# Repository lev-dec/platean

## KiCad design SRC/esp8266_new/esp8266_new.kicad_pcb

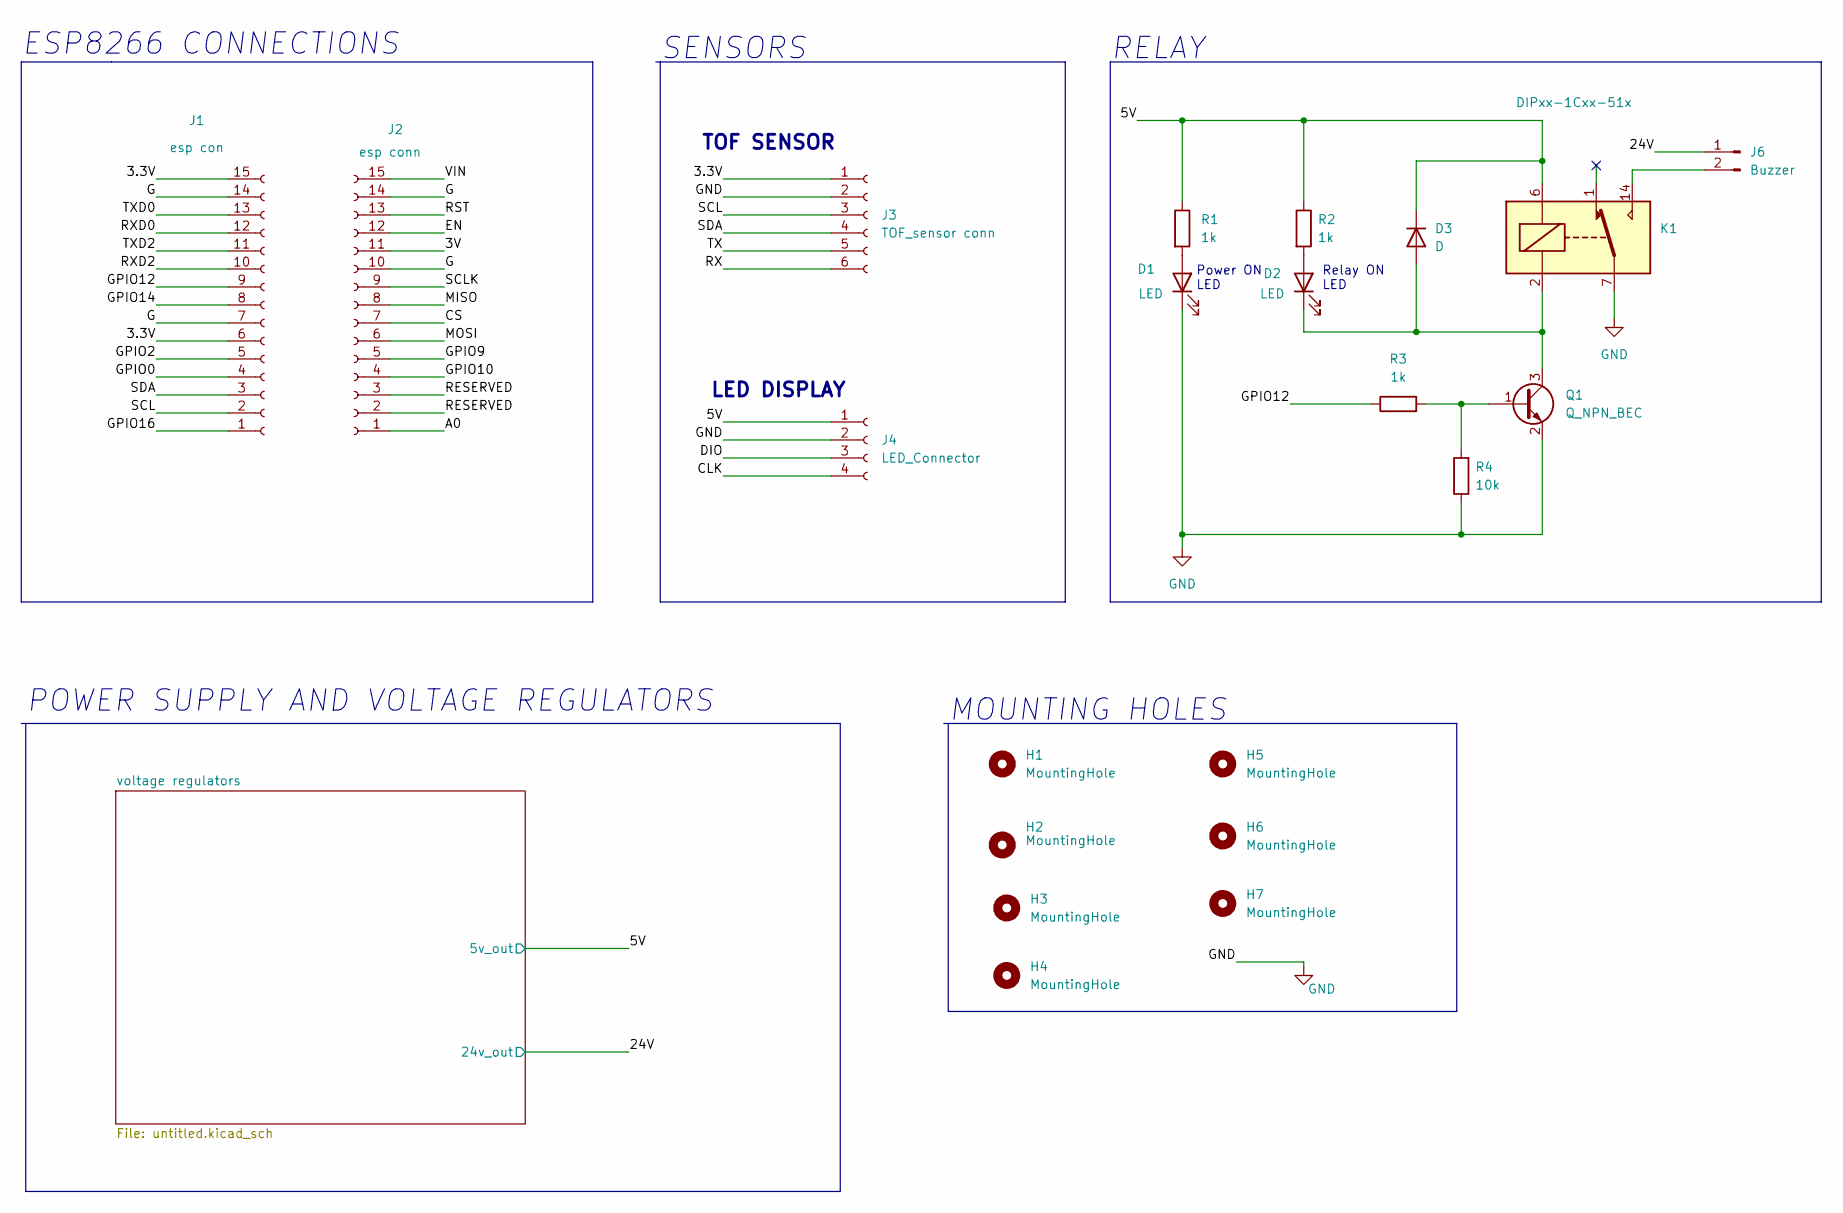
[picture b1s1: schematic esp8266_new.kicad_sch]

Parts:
D1, D2: LED; LED_0603_1608Metric
D3: D; SOT-23
H1, H2, H3, H4, H5, H6, H7: MountingHole; MountingHole_2mm
J1: esp con; PinSocket_1x15_P2.54mm_Vertical
J2: esp conn; PinSocket_1x15_P2.54mm_Vertical
J3: TOF_sensor conn; PinSocket_1x06_P2.54mm_Horizontal
J4: LED_Connector; PinSocket_1x04_P2.54mm_Horizontal
J6: Buzzer; JST_EH_S2B-EH_1x02_P2.50mm_Horizontal
K1: DIPxx-1Cxx-51x; Relay_StandexMeder_DIP_LowProfile
Q1: Q_NPN_BEC; TO-252-3_TabPin2
R1, R2, R3: 1k; R_0603_1608Metric
R4: 10k; R_0603_1608Metric

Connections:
/3.3V: J1.6, J1.15, J3.1
/3V: J2.11
/5V: D3.1 (K), J4.1, K1.6, R1.1, R2.1; also elsewhere on the board
/24V: J6.1; also elsewhere on the board
/A0: J2.1
/CLK: J4.4
/CS: J2.7
/DIO: J4.3
/EN: J2.12
/G: J1.7, J1.14, J2.10, J2.14
/GPIO0: J1.4
/GPIO2: J1.5
/GPIO9: J2.5
/GPIO10: J2.4
/GPIO12: J1.9, R3.1
/GPIO14: J1.8
/GPIO16: J1.1
/MISO: J2.8
/MOSI: J2.6
/RESERVED: J2.2, J2.3
/RST: J2.13
/RX: J3.6
/RXD0: J1.12
/RXD2: J1.10
/SCL: J1.2, J3.3
/SCLK: J2.9
/SDA: J1.3, J3.4
/TX: J3.5
/TXD0: J1.13
/TXD2: J1.11
/VIN: J2.15
GND: D1.1 (K), J3.2, J4.2, K1.7, K1.8, Q1.2 (E), R4.1; also elsewhere on the board
unnamed: D1.2 (A), R1.2
unnamed: D2.1 (K), D3.2 (A), K1.2, Q1.3 (C)
unnamed: D2.2 (A), R2.2
unnamed: J6.2, K1.14
unnamed: Q1.1 (B), R3.2, R4.2

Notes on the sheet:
LED DISPLAY
TOF SENSOR
Relay ON LED
POWER SUPPLY AND VOLTAGE REGULATORS
SENSORS
Power ON LED
MOUNTING HOLES
RELAY
ESP8266 CONNECTIONS

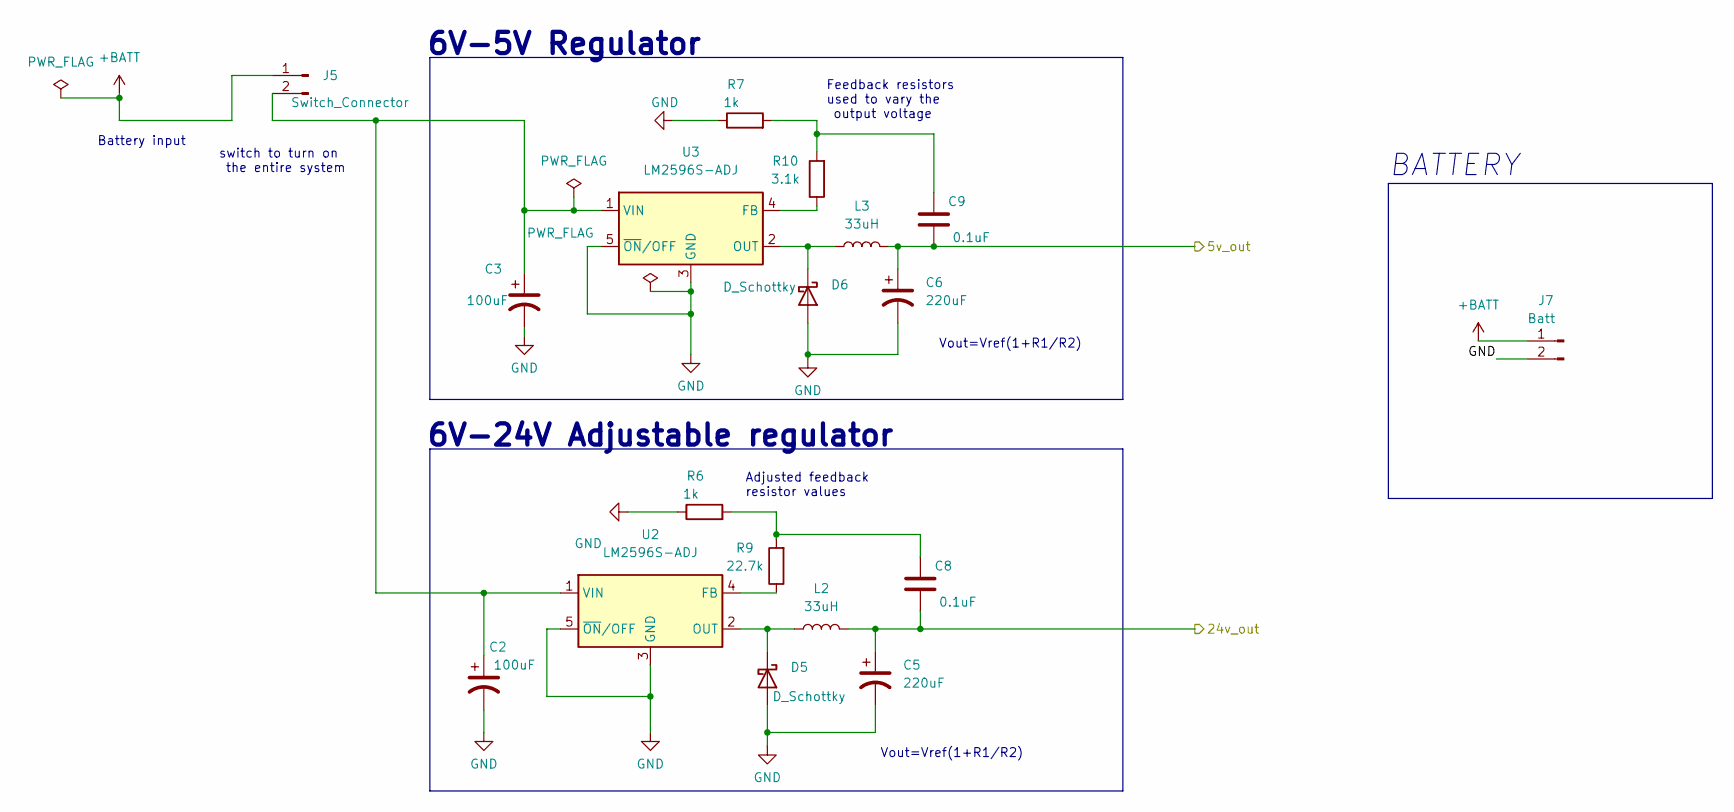
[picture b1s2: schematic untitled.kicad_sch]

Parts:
C2, C3: 100uF; C_0603_1608Metric
C5, C6: 220uF; C_1210_3225Metric
C8, C9: 0.1uF; CP_Elec_4x5.8
D5, D6: D_Schottky; TO-277A
J5: Switch_Connector; JST_EH_S2B-EH_1x02_P2.50mm_Horizontal
J7: Batt; JST_EH_S2B-EH_1x02_P2.50mm_Horizontal
L2, L3: 33uH; L_1206_3216Metric
R6, R7: 1k; R_0603_1608Metric
R9: 22.7k; R_0603_1608Metric
R10: 3.1k; R_0603_1608Metric
U2, U3: LM2596S-ADJ; TO-263-5_TabPin3

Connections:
+BATT: J5.1, J7.1
/5V: C6.1, C9.2, L3.2; also elsewhere on the board
/24V: C5.1, C8.2, L2.2; also elsewhere on the board
GND: C2.2, C3.2, C5.2, C6.2, D5.2 (A), D6.2 (A), J7.2, R6.1, R7.1, U2.3 (GND), U2.5 (~ON/OFF), U3.3 (GND), U3.5 (~ON/OFF); also elsewhere on the board
unnamed: C2.1, C3.1, J5.2, U2.1 (VIN), U3.1 (VIN)
unnamed: C8.1, R6.2, R9.2
unnamed: C9.1, R7.2, R10.2
unnamed: D5.1 (K), L2.1, U2.2 (OUT)
unnamed: D6.1 (K), L3.1, U3.2 (OUT)
unnamed: R9.1, U2.4 (FB)
unnamed: R10.1, U3.4 (FB)

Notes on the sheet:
6V-24V Adjustable regulator
Feedback resistors used to vary the output voltage
Adjusted feedback resistor values
Battery input
BATTERY
switch to turn on the entire system
6V-5V Regulator
Vout=Vref(1+R1/R2)

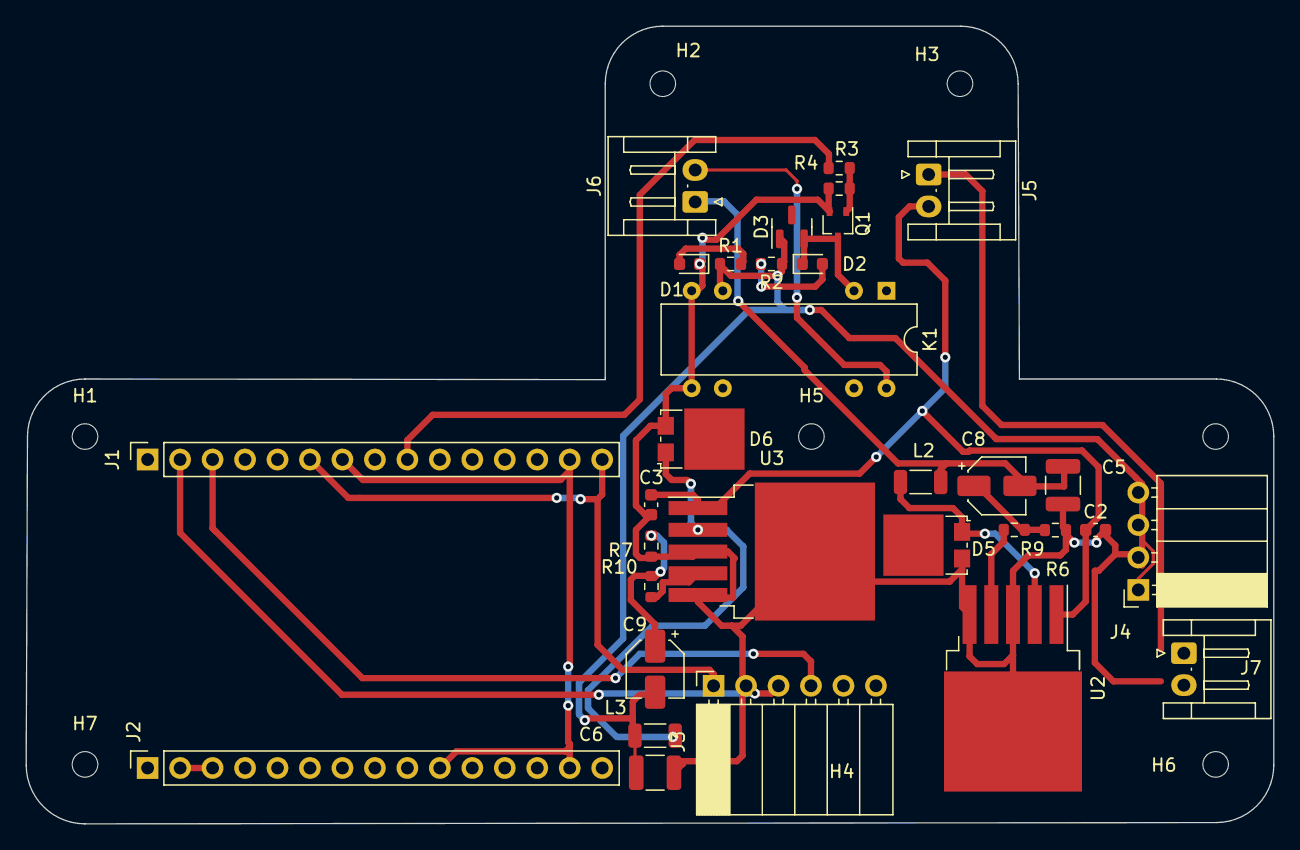
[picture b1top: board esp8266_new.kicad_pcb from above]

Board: 2 copper layers, 97.6 x 62.4 mm, 39 parts (0 on the bottom side), 22 nets.
